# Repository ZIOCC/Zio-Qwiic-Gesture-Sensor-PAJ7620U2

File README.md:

# Zio Qwiic Gesture Sensor (PAJ7620U2)

> This product can be available for purchase [here](https://www.smart-prototyping.com/Zio-Qwiic-Gesture-Sensor-PAJ7620U2).

#### Description

This is a Qwiic breakout board based on PAJ7620U2. It can recognize 9 human hand gesticulations such as moving up, down, left, right, forward, backward, circle-clockwise, circle-counter clockwise, and waving. 

The normal gesture detecting range is 5 to 15 cm, and the operating view angle is at 60° diagonally. The PAC7620 also offer built-in proximity detection for the purpose of sensing an object approaching or departing.

As it is a [Qwiic compatible](https://www.smart-prototyping.com/Qwiic.html) module, you can use [Qwiic cable](https://www.smart-prototyping.com/zio-cables) to daisy chain it with other Qwiic devices, no need soldering and jumper wire connecting!

#### Specification

* Operation Voltage: 3.3V
* Current: 2.3mA
* Gesture speed: 60~600°/s in normal mode
* Interface: I2C
* IC: PAJ7620U2
* I2C address: 0x73
* Dimension: 26.3 x 23.3mm
* Weight: 1.6g

#### Links
* [PCB Source file](https://github.com/ZIOCC/Zio-Qwiic-Gesture-Sensor-PAJ7620U2/tree/master/EAGLE)
* [PCB schematic](https://github.com/ZIOCC/Zio-Qwiic-Gesture-Sensor-PAJ7620U2/blob/master/zio%20qwiic%20gestuer%20sensor%20PAJ7620U2%20schematic.pdf)
* [Demo code](https://github.com/Seeed-Studio/Gesture_PAJ7620)
* [Sensor PAC7620 Datasheet](https://github.com/ZIOCC/Zio-Qwiic-Gesture-Sensor-PAJ7620U2/blob/master/PAJ7620U2_datasheet.pdf)

###### About Zio
> Zio is a new line of open sourced, compact, and grid layout boards, fully integrated for Arduino and Qwiic ecosystem. Designed ideally for wearables, robotics, small-space limitations or other on the go projects. Check out other awesome Zio products [here](https://www.smart-prototyping.com/Zio).

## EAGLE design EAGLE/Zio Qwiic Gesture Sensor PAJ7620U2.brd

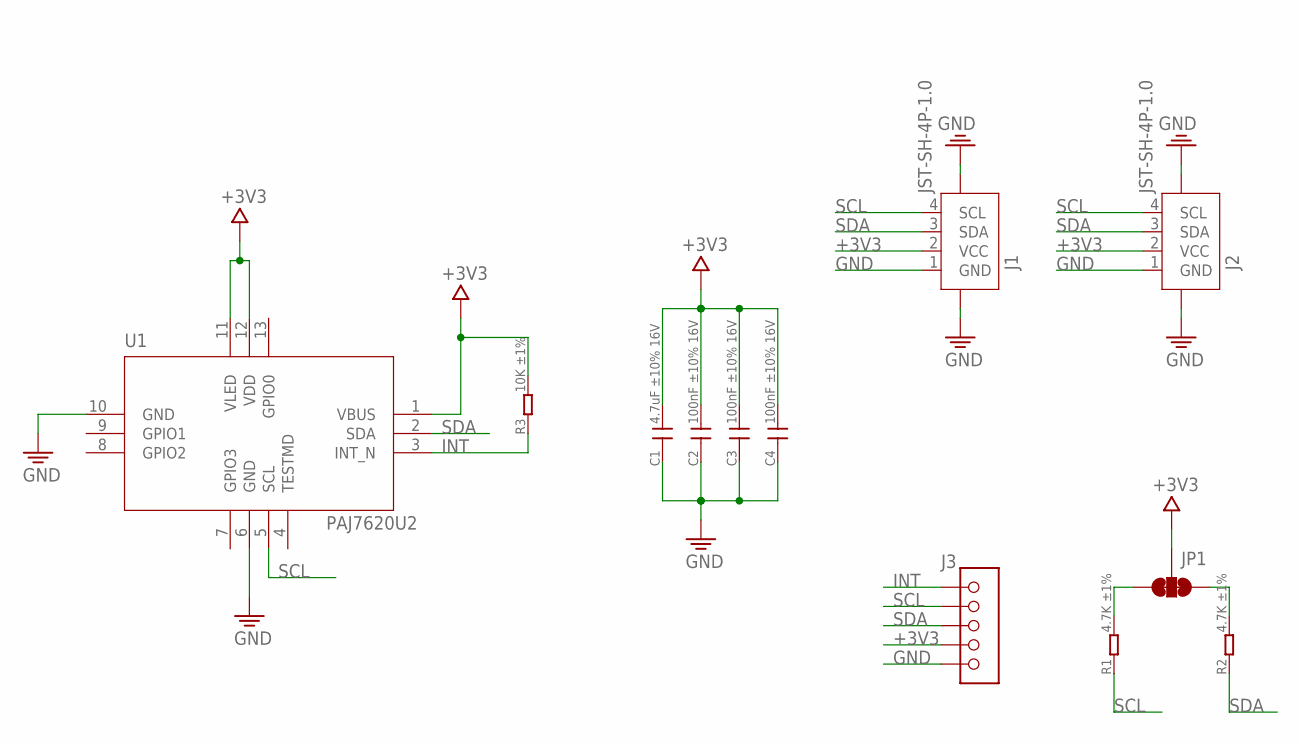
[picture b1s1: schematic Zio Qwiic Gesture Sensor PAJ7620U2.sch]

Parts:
C1: 4.7uF ±10% 16V; C0603
C2, C3, C4: 100nF ±10% 16V; C0603
J1, J2: JST-SH-4P-1.0; JST-SH-4P
J3: HEADER-5P-2.54; 5P-2.54
JP1: SMT-JUMPER_3_2-NC_TRACE
R1, R2: 4.7K ±1%; R0603
R3: 10K ±1%; R0603
U1: PAJ7620U2

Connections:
+3V3: C1.2, C2.2, C3.2, C4.2, J1.2 (VCC), J2.2 (VCC), J3.4, JP1.2, R3.2, U1.1 (VBUS), U1.11 (VLED), U1.12 (VDD)
GND: C1.1, C2.1, C3.1, C4.1, J1.1 (GND), J1.NC1 (5), J1.NC2 (6), J2.1 (GND), J2.NC1 (5), J2.NC2 (6), J3.5, U1.6 (GND), U1.10 (GND)
INT: J3.1, R3.1, U1.3 (INT_N)
unnamed: JP1.3, R1.2
unnamed: JP1.1, R2.2
SCL: J1.4 (SCL), J2.4 (SCL), J3.2, R1.1, U1.5 (SCL)
SDA: J1.3 (SDA), J2.3 (SDA), J3.3, R2.1, U1.2 (SDA)

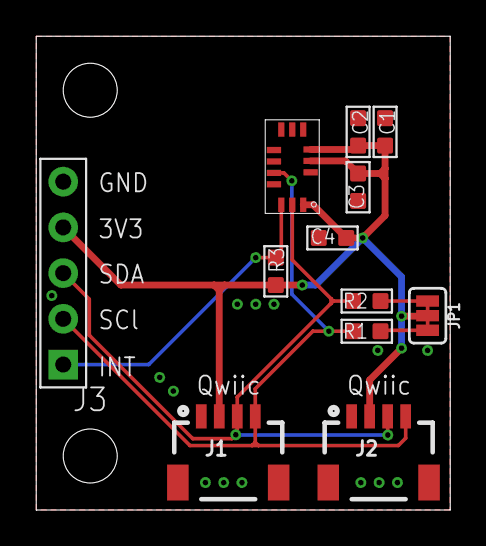
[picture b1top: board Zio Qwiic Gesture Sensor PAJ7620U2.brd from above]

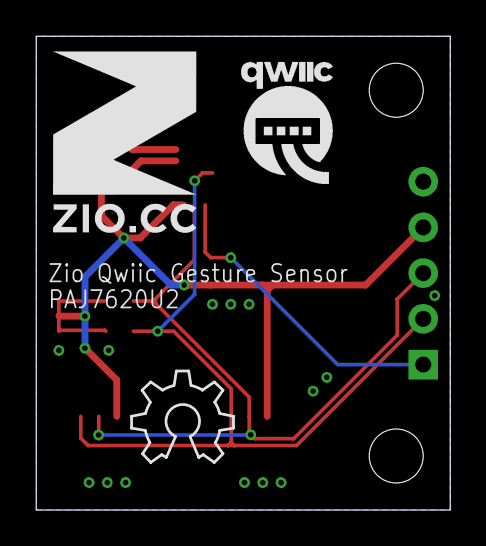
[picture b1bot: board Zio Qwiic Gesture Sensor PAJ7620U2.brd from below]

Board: 2 copper layers, 23.0 x 26.3 mm, 15 parts (3 on the bottom side), 7 nets.

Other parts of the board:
U$4: 10MM
U$5: QWIIC-LOGO-MEDIUM
U$6: OSHW_6X200_NOTEXT
